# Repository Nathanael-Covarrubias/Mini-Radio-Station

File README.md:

# Mini-Radio-Station
FM Transmitter-NS73M

This project is a simple FM Transmitter that is deisgned to be a module for the M5 Stick C Plus. Here is a link to the parts on Digikey https://www.digikey.com/en/mylists/list/XUSR3FV555. However, the NS73M is no longer active, so it's not in the Digikey Cart but if you have one feel free to try this simple design. The xlsx file is just a Excel Sheet with information on each part.

The pdf's are just print out's of the eagle schematic and board. They are simply for reference. The Eagle files are the library or .lbr (which contains all the necessary components for the PCB), the schematic or .sch (which contains the PCB symbols), and the board or .brd (which has the actual pcb layout). This project does have Boards on OSHPark already and it is called Mini Radio Station.

The stl files are the case files that are ready to be 3D printed. If any modifications want to be made the f3d file is the actual fusion 360 drawing. 

Lastly, the arduino code is the ino file. This code is incomplete as the module can only be on one frequency, but you can reprogram it to be on the appropriate frequency. With some improvement a better version would allow the buttons on the M5 Stick C Plus to change frequencies. I would suggest using https://github.com/poelstra/arduino-multi-button.

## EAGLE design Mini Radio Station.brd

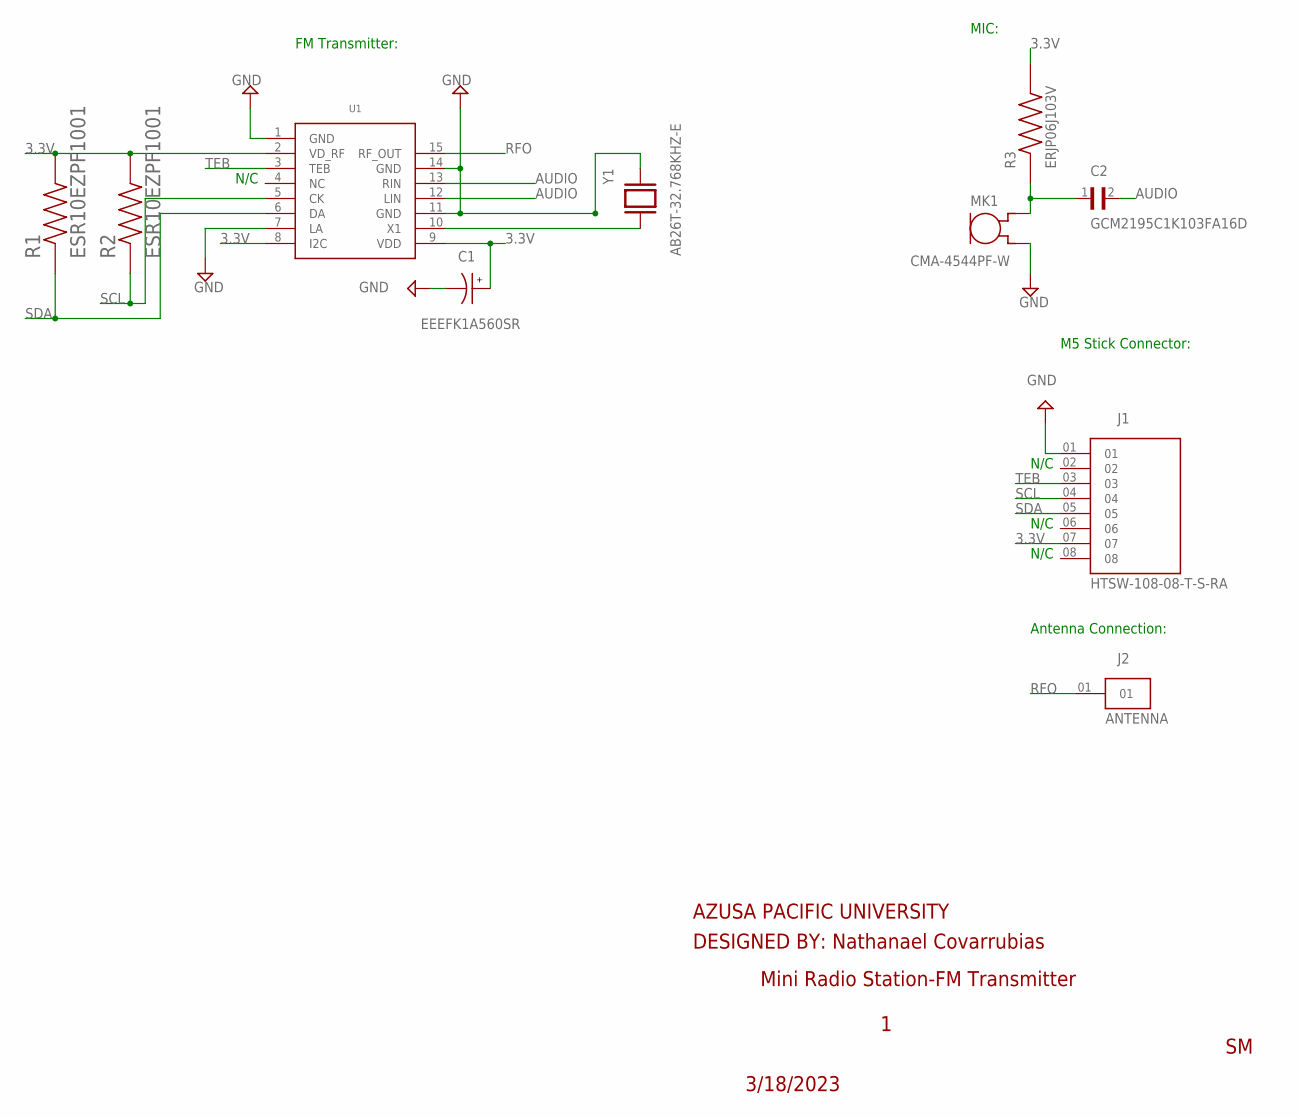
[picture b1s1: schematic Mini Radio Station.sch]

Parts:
C1: EEEFK1A560SR; CAP_EEEFK1A560SR
C2: GCM2195C1K103FA16D; CAPC2012X95N
J1: HTSW-108-08-T-S-RA; SAMTEC_HTSW-108-08-T-S-RA
J2: ANTENNA
MK1: CMA-4544PF-W; MIC_CMA-4544PF-W
R1, R2: ESR10EZPF1001; RESC2012X65N
R3: ERJP06J103V; RES_ERJP06J103V
U1: NS73M
Y1: AB26T-32.768KHZ-E; XTAL_AB26T-32.768KHZ-E

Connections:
3.3V: C1.1, J1.07, R1.2, R2.2, R3.2, U1.2 (VD_RF), U1.8 (I2C), U1.9 (VDD)
AUDIO: C2.2, U1.12 (LIN), U1.13 (RIN)
GND: C1.2, J1.01, MK1.2 (GND), U1.1 (GND), U1.7 (LA), U1.11 (GND), U1.14 (GND), Y1.1
unnamed: U1.10 (X1), Y1.2
unnamed: C2.1, MK1.1 (OUT), R3.1
RFO: J2.01, U1.15 (RF_OUT)
SCL: J1.04, R2.1, U1.5 (CK)
SDA: J1.05, R1.1, U1.6 (DA)
TEB: J1.03, U1.3 (TEB)

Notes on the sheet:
Mini Radio Station-FM Transmitter
3/18/2023
AZUSA PACIFIC UNIVERSITY
DESIGNED BY: Nathanael Covarrubias
N/C
FM Transmitter:
MIC:
M5 Stick Connector:
Antenna Connection:

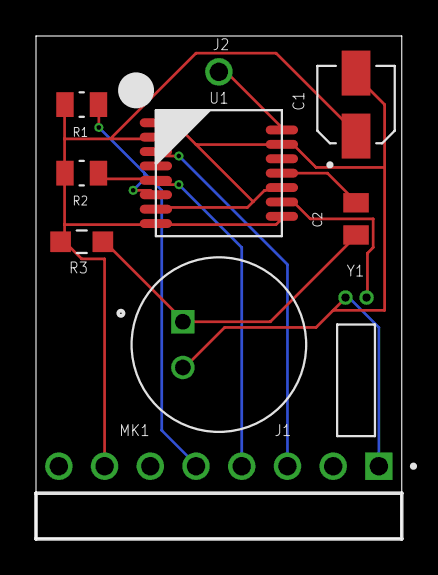
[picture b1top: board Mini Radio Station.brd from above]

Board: 2 copper layers, 20.3 x 27.9 mm, 10 parts (0 on the bottom side), 9 nets.
